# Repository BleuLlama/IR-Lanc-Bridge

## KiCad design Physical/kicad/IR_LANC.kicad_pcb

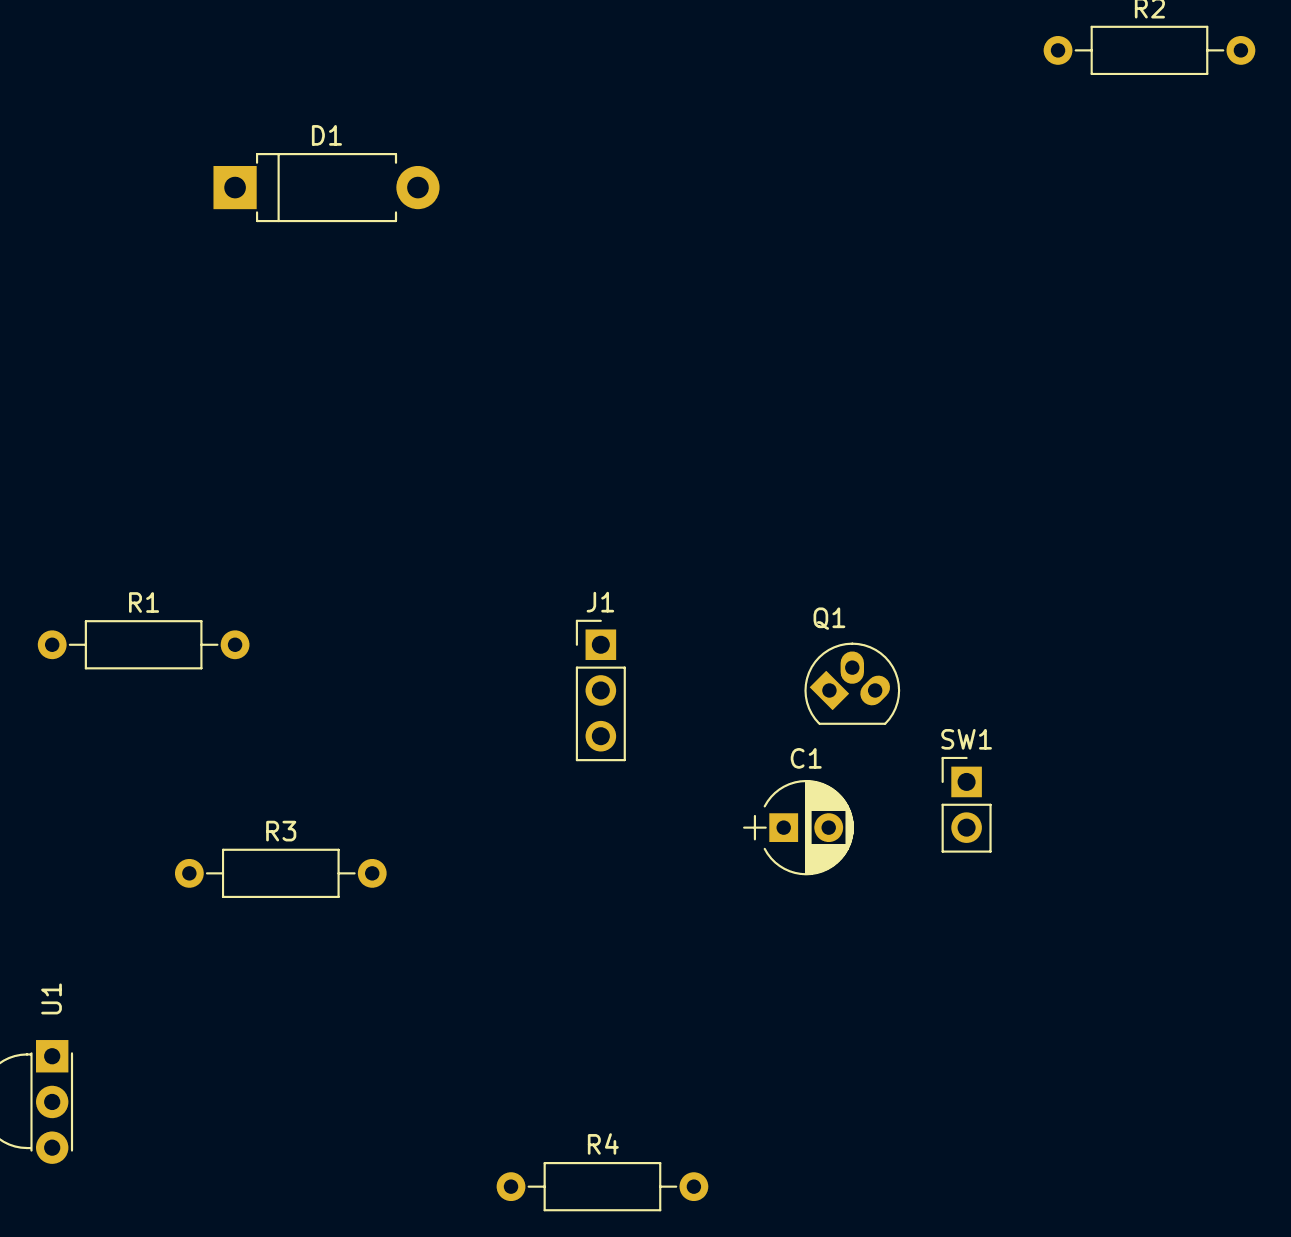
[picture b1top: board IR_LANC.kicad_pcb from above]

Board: 2 copper layers, 10 parts (0 on the bottom side), 5 nets, no tracks yet.

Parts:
C1: 4.7u; CP_Radial_D5.0mm_P2.50mm
D1: 5.1v Zener; D_DO-15_P10.16mm_Horizontal
J1: 2.5mm jack/plug; PinHeader_1x03_P2.54mm_Vertical
Q1: 2N3904/BC547; TO-92_Molded_Narrow_Oval
R1: 4k7; R_Axial_DIN0207_L6.3mm_D2.5mm_P10.16mm_Horizontal
R2: 5k6; R_Axial_DIN0207_L6.3mm_D2.5mm_P10.16mm_Horizontal
R3: 100R; R_Axial_DIN0207_L6.3mm_D2.5mm_P10.16mm_Horizontal
R4: 12k; R_Axial_DIN0207_L6.3mm_D2.5mm_P10.16mm_Horizontal
SW1: SW_SPST; PinHeader_1x02_P2.54mm_Vertical
U1: IR Rx module; IRReceiver_Vishay_MINIMOLD-3pin

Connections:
+5V: C1.1, R1.1, R4.2, SW1.2, U1.2
GND: C1.2, D1.2, Q1.1, U1.3
unnamed: D1.1, Q1.3, R1.2
unnamed: Q1.2, R2.1
unnamed: R3.1, R4.1, U1.1

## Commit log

2020-07-27 Initial checkin
